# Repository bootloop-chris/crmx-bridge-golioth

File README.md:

# CRMX Bridge

An early demo of the [BootLoop Agent](https://bootloop.ai)!

*This repo is forked from a personal project of mine [https://github.com/chris-markus/crmx-bridge](https://github.com/chris-markus/crmx-bridge). Some clean-up commits added and upgraded to work with the most recent version of the IDF.*

Commit [77b8aad](https://github.com/bootloop-chris/crmx-bridge-golioth/commit/77b8aad5b4f520016bc5265554ae8e2e5ca4bd7b) was entirely generated and tested end-to-end by the BootLoop Agent. Email `chris [AT] bootloop [DOT] ai` for a video of the process.

---

Original README below:

Firmware and hardware for a CRMX bridge based around an ESP32s3 and a [TimoTwo module](https://lumenradio.com/products/timotwo/).

## Caveats

This is a personal project under active development. There are known (and probably unknown) bugs in the hardware. It has been open-sourced for visibility but use the hardware and firmware at your own risk!

### Known Issues

* The power button circuit has no memory outside of the microcontroller, so while downloading firmware, one of two things must be done:
  * Jump J105 to disable the power button circuit and unconditionally power the device while USB is connected
  * Hold down the power button for the duration of the software update

## Contents

* [crmx-bridge](./crmx-bridge/) - Hardware design files for the main PCBA
* [crmx-bridge-hmi](./crmx-bridge-hmi/) - Hardware design files for the Interface PCBA
* [crmx-bridge-firmware](./crmx-bridge-firmware/) - Firmware for the ESP32s3

## Firmware

Note that the firmware is pretty incomplete. It has a subset of functionality (can forward wired DMX to CRMX) but lacks control over most settings via the HMI among other omissions.

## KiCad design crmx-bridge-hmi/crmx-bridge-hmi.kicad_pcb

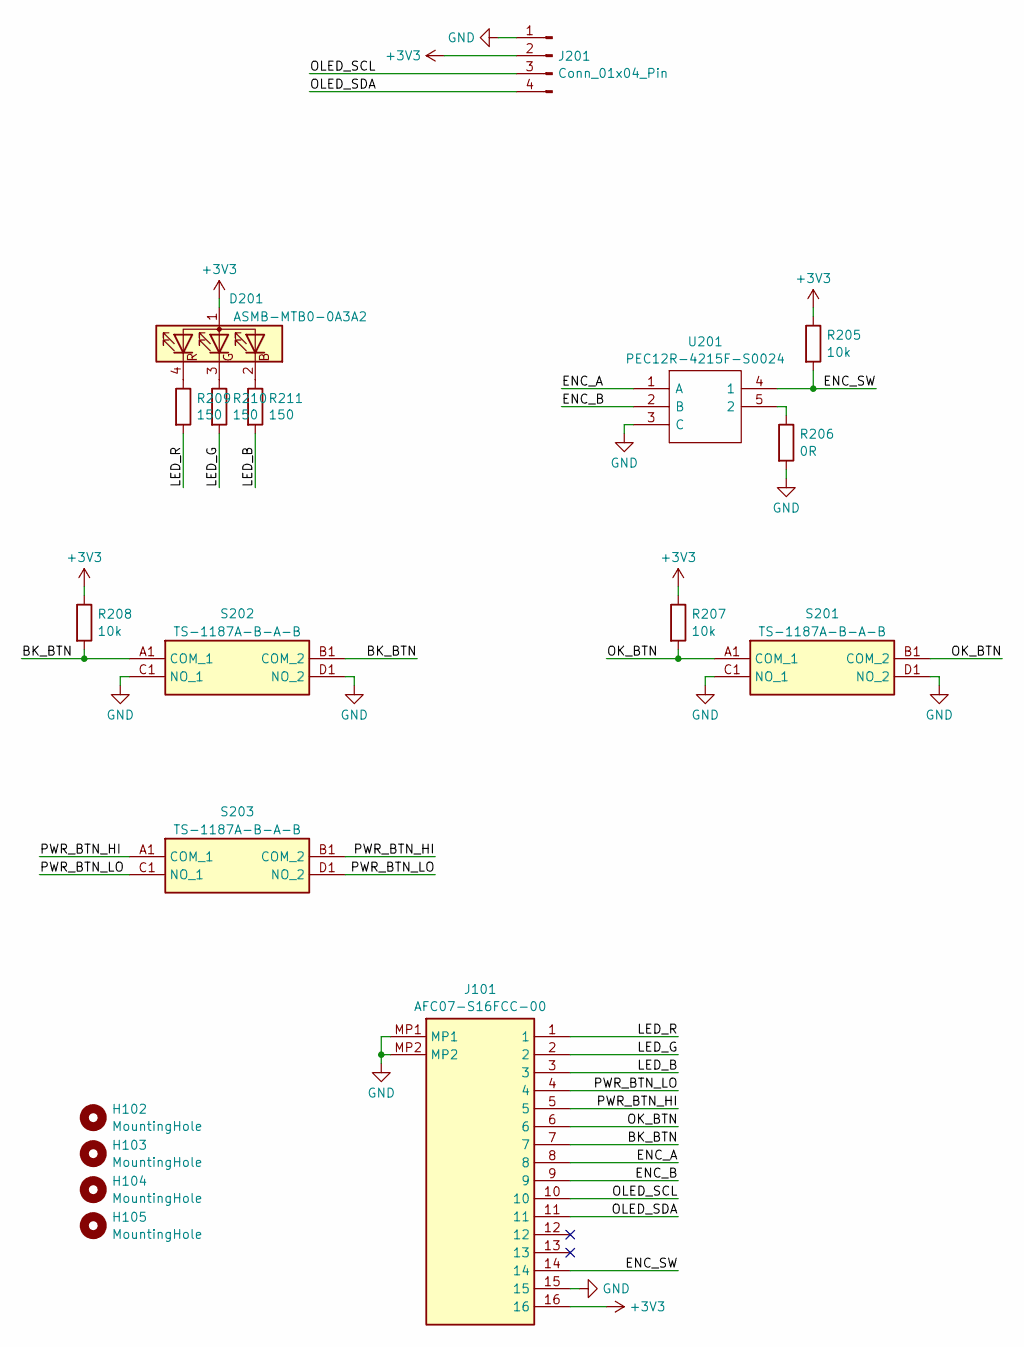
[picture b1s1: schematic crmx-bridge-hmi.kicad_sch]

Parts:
D201: ASMB-MTB0-0A3A2; ASMBMTB00A3A2
H102, H103, H104, H105: MountingHole; MountingHole_3.2mm_M3
J101: AFC07-S16FCC-00; AFC07S16FCC00; Manufacturer_Part_Number AFC07-S16FCC-00; LCSC C11053
J201: Conn_01x04_Pin; OLED_1.3
R205, R207, R208: 10k; R_0402_1005Metric; LCSC C25744
R206: 0R; R_0402_1005Metric; LCSC C17168
R209, R210, R211: 150; R_0603_1608Metric; LCSC C22808
S201, S202, S203: TS-1187A-B-A-B; TS1187ABAB; Manufacturer_Part_Number TS-1187A-B-A-B; LCSC C318884
U201: PEC12R-4215F-S0024; PEC12R-4XXXF-SXXXX; Manufacturer_Part_Number PEC12R-4215F-S0024; Mouser Part Number 652-PEC12R-4215F-S24

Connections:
+3V3: D201.1 (A), J101.16, J201.2, R205.1, R207.1, R208.1
/BK_BTN: J101.7, R208.2, S202.A1 (COM_1), S202.B1 (COM_2)
/ENC_A: J101.8, U201.1 (A)
/ENC_B: J101.9, U201.2 (B)
/ENC_SW: J101.14, R205.2, U201.4 (1)
/LED_B: J101.3, R211.2
/LED_G: J101.2, R210.2
/LED_R: J101.1, R209.2
/OK_BTN: J101.6, R207.2, S201.A1 (COM_1), S201.B1 (COM_2)
/OLED_SCL: J101.10, J201.3
/OLED_SDA: J101.11, J201.4
/PWR_BTN_HI: J101.5, S203.A1 (COM_1), S203.B1 (COM_2)
/PWR_BTN_LO: J101.4, S203.C1 (NO_1), S203.D1 (NO_2)
GND: J101.15, J101.MP1, J101.MP2, J201.1, R206.2, S201.C1 (NO_1), S201.D1 (NO_2), S202.C1 (NO_1), S202.D1 (NO_2), U201.3 (C)
unnamed: D201.2 (BK), R211.1
unnamed: D201.3 (GK), R210.1
unnamed: D201.4 (RK), R209.1
unnamed: R206.1, U201.5 (2)

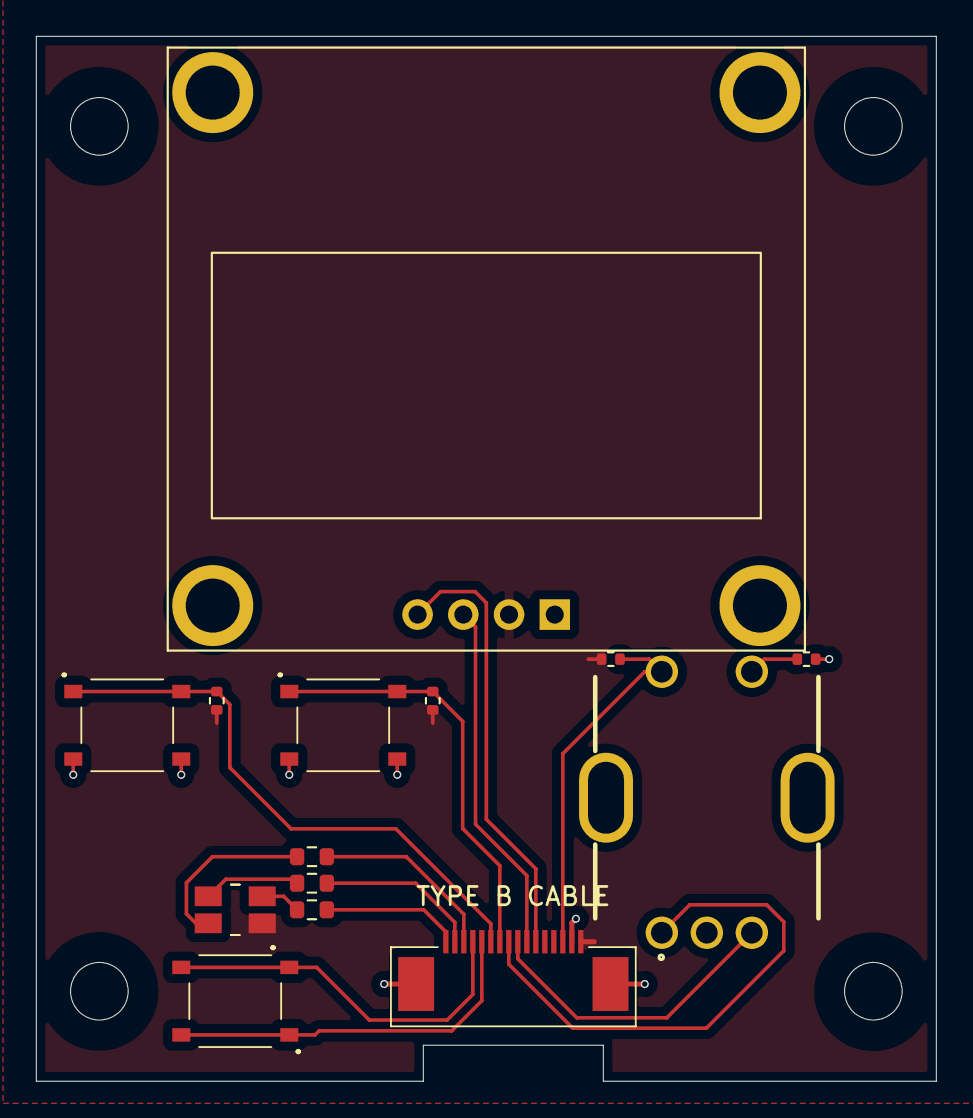
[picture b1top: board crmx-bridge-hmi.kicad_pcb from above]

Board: 2 copper layers, 50.0 x 58.0 mm, 18 parts (0 on the bottom side), 18 nets.

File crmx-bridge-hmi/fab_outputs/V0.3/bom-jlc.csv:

Designator,Footprint,Quantity,Value,LCSC Part #
J101,AFC07S16FCC00,1,AFC07-S16FCC-00,C11053
"R205, R207, R208",0402,3,10k,C25744
R206,0402,1,0R,C17168
"R209, R210, R211",0603,3,150,C22808
"S201, S202, S203",TS1187ABAB,3,TS-1187A-B-A-B,C318884

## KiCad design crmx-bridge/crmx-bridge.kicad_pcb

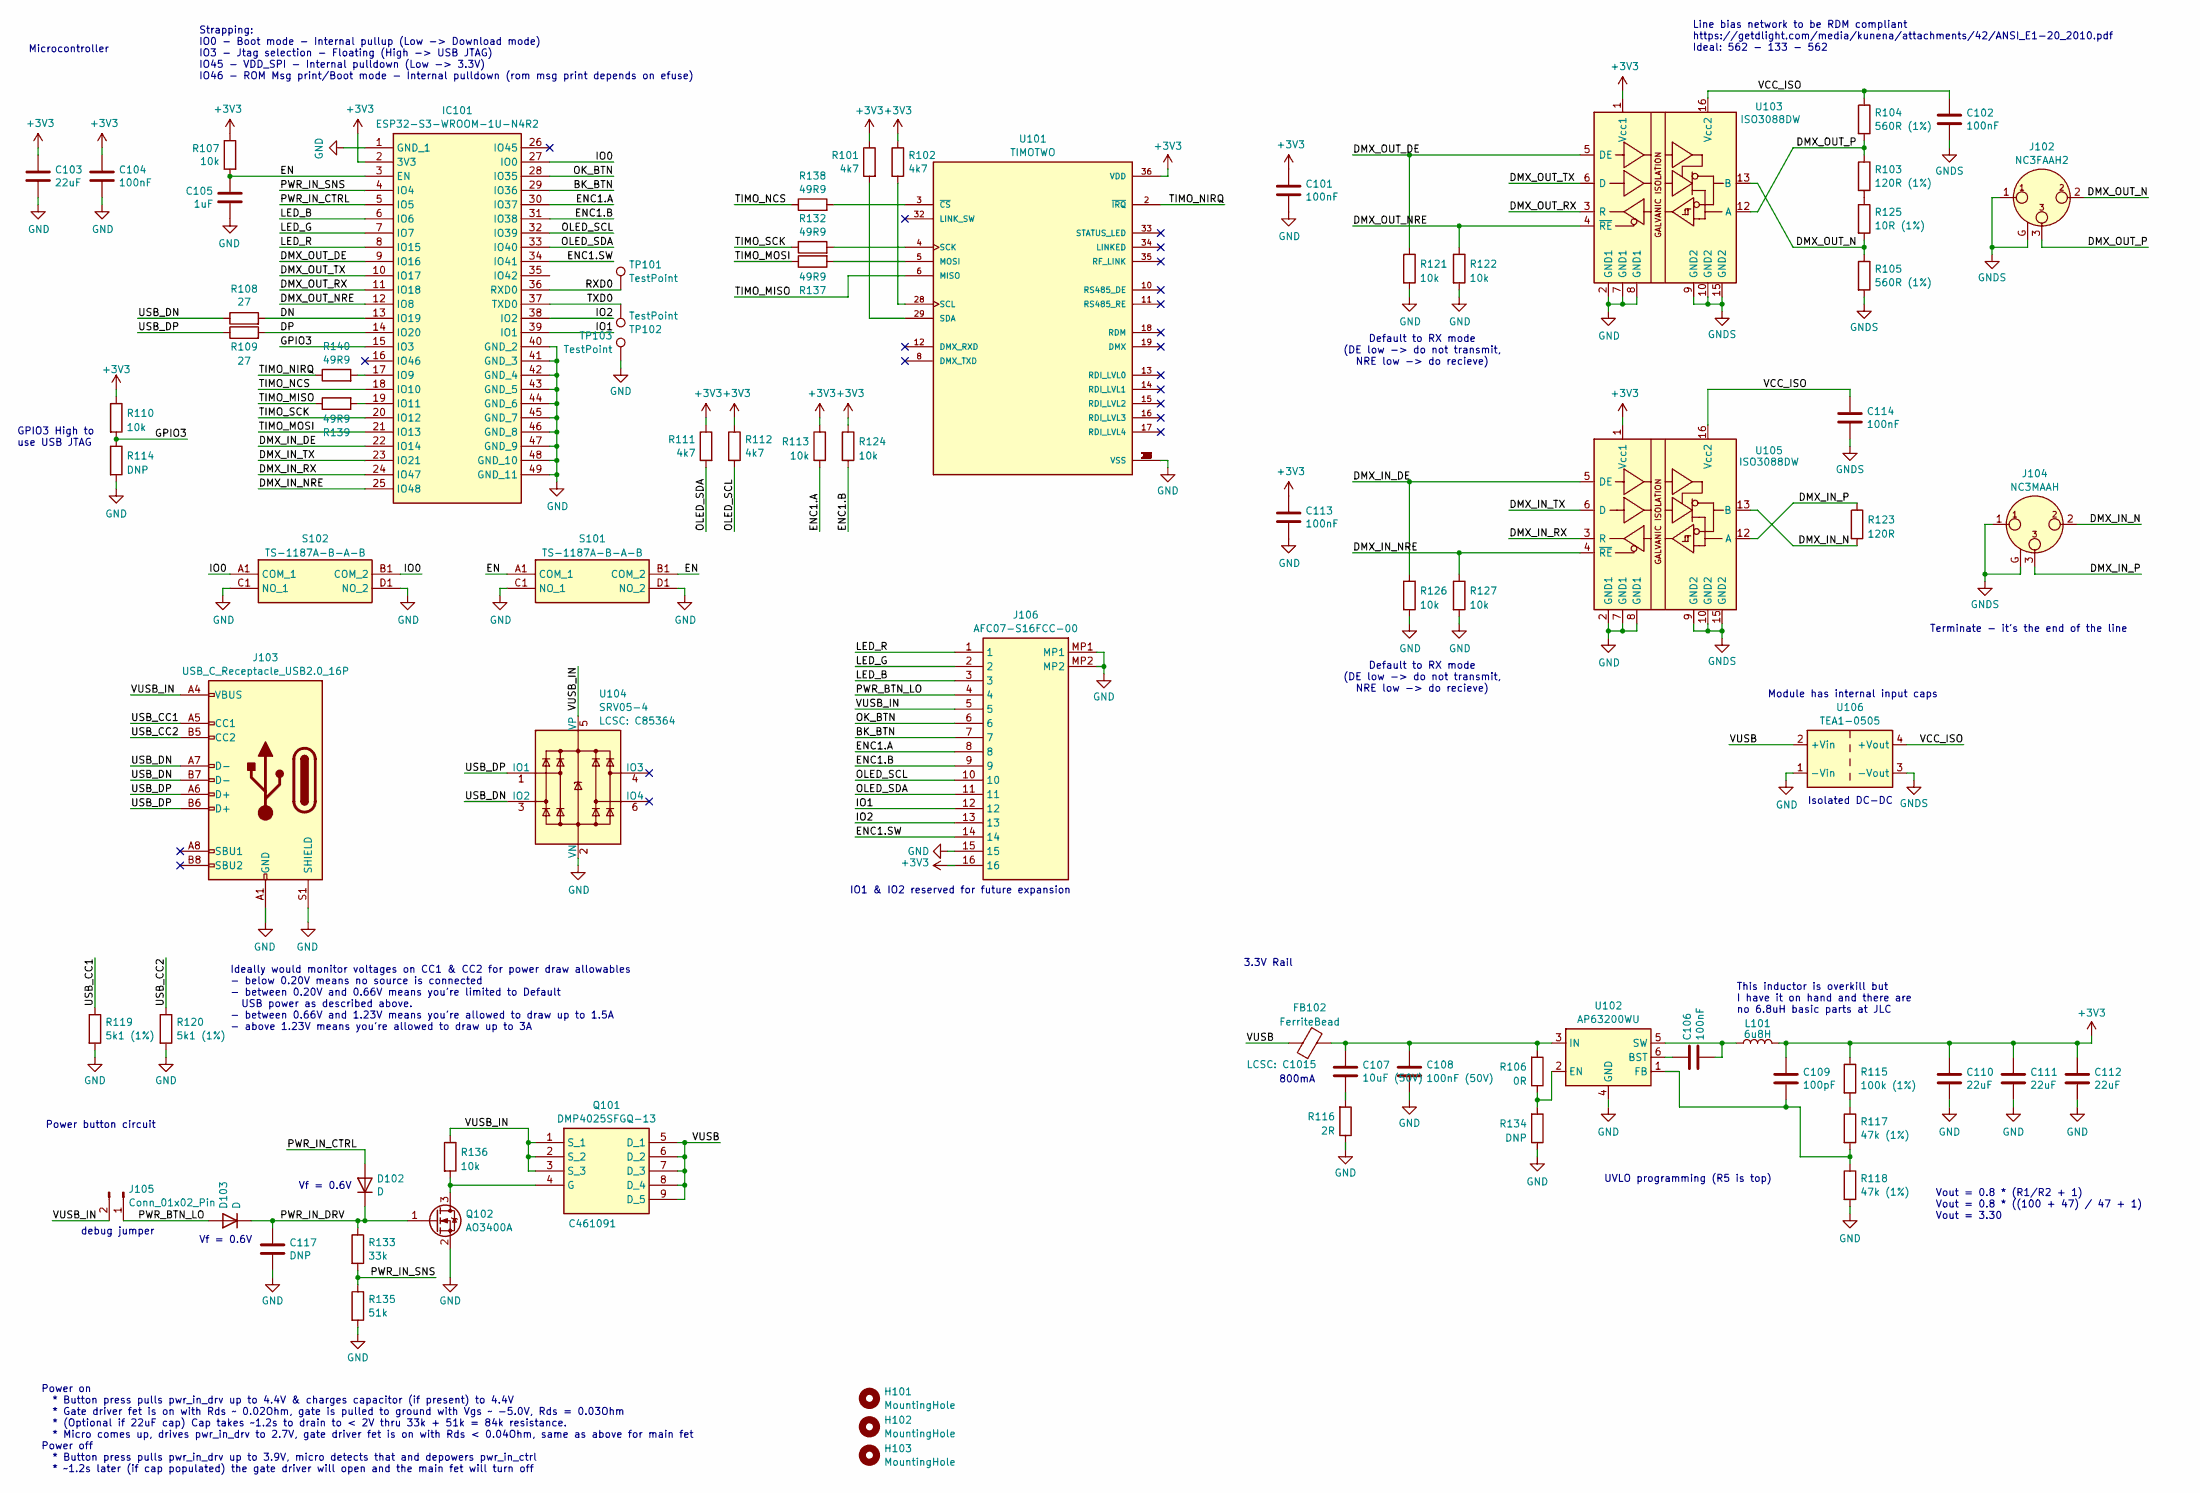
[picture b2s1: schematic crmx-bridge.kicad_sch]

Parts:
C101, C102, C104, C106, C113, C114: 100nF; C_0402_1005Metric; LCSC C1525
C103, C110, C111, C112: 22uF; C_1206_3216Metric; LCSC C12891
C105: 1uF; C_0603_1608Metric; LCSC C15849
C107: 10uF (50V); C_0603_1608Metric; LCSC C96446
C108: 100nF (50V); C_0402_1005Metric; LCSC C1525
C109: 100pF; C_0603_1608Metric; LCSC C14858
C117: DNP; C_1206_3216Metric; LCSC C12891
D102, D103: D; D_SOD-323; LCSC C191023
FB102: FerriteBead; C_0805_2012Metric; LCSC C1015
H101, H102, H103: MountingHole; MountingHole_3.2mm_M3
IC101: ESP32-S3-WROOM-1U-N4R2; ESP32S3WROOM1UN4R2; Manufacturer_Part_Number ESP32-S3-WROOM-1U-N4R2; Mouser Part Number 356-ESP32S3WRM1UN4R2
J102: NC3FAAH2; Jack_XLR_Neutrik_NC3FAAH2_Horizontal
J103: USB_C_Receptacle_USB2.0_16P; USB_C_Receptacle_HRO_TYPE-C-31-M-12; LCSC C165948
J104: NC3MAAH; Jack_XLR_Neutrik_NC3MAAH_Horizontal
J105: Conn_01x02_Pin; PinHeader_1x02_P2.54mm_Vertical
J106: AFC07-S16FCC-00; AFC07S16FCC00; Manufacturer_Part_Number AFC07-S16FCC-00; LCSC C11053
L101: 6u8H; L_Bourns_SRP7028A_7.3x6.6mm
Q101: DMP4025SFGQ-13; DMTH8008LFGQ7; Manufacturer_Part_Number DMPH4029LFGQ-13; Mouser Part Number 621-DMPH4029LFGQ-13
Q102: AO3400A; SOT-23; LCSC C20917
R101, R102, R111, R112: 4k7; R_0402_1005Metric; LCSC C25900
R103: 120R (1%); R_0603_1608Metric; LCSC C22787
R104, R105: 560R (1%); R_0603_1608Metric; LCSC C23204
R106: 0R; R_0402_1005Metric; LCSC C17168
R107, R110, R113, R121, R122, R124, R126, R127, R136: 10k; R_0402_1005Metric; LCSC C25744
R108, R109: 27; R_0603_1608Metric; LCSC C25190
R114, R134: DNP; R_0402_1005Metric
R115: 100k (1%); R_0402_1005Metric; LCSC C25741
R116: 2R; R_0603_1608Metric; LCSC C22977
R117, R118: 47k (1%); R_0402_1005Metric; LCSC C25792
R119, R120: 5k1 (1%); R_0402_1005Metric; LCSC C25905
R123: 120R; R_0603_1608Metric; LCSC C22787
R125: 10R (1%); R_0603_1608Metric; LCSC C22859
R132, R137, R138, R139, R140: 49R9; R_0402_1005Metric; LCSC C25120
R133: 33k; R_0402_1005Metric; LCSC C25779
R135: 51k; R_0402_1005Metric; LCSC C25794
S101, S102: TS-1187A-B-A-B; TS1187ABAB; Manufacturer_Part_Number TS-1187A-B-A-B; LCSC C318884
TP101, TP102, TP103: TestPoint; TestPoint_Pad_D1.5mm
U101: TIMOTWO; MODULE_TIMOTWO; PARTREV N/A
U102: AP63200WU; TSOT-23-6; LCSC C2071868
U103, U105: ISO3088DW; SOIC-16W_7.5x10.3mm_P1.27mm; LCSC C39386
U104: SRV05-4; SOT-23-6; LCSC C85364
U106: TEA1-0505; Converter_DCDC_TRACO_TEA1-xxxx_THT

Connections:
+3V3: C101.1, C103.1, C104.1, C109.1, C110.1, C111.1, C112.1, C113.1, IC101.2 (3V3), J106.16, L101.2, R101.1, R102.1, R107.1, R110.1, R111.1, R112.1, R113.1, R115.1, R124.1, U101.36 (VDD), U103.1 (Vcc1), U105.1 (Vcc1)
/BK_BTN: IC101.29 (IO36), J106.7
/DMX_IN_DE: IC101.22 (IO14), R126.1, U105.5 (DE)
/DMX_IN_N: J104.2, R123.2, U105.13 (B)
/DMX_IN_NRE: IC101.25 (IO48), R127.1, U105.4 (~RE)
/DMX_IN_P: J104.3, R123.1, U105.12 (A)
/DMX_IN_RX: IC101.24 (IO47), U105.3 (R)
/DMX_IN_TX: IC101.23 (IO21), U105.6 (D)
/DMX_OUT_DE: IC101.9 (IO16), R121.1, U103.5 (DE)
/DMX_OUT_N: J102.2, R105.1, R125.2, U103.13 (B)
/DMX_OUT_NRE: IC101.12 (IO8), R122.1, U103.4 (~RE)
/DMX_OUT_P: J102.3, R103.1, R104.2, U103.12 (A)
/DMX_OUT_RX: IC101.11 (IO18), U103.3 (R)
/DMX_OUT_TX: IC101.10 (IO17), U103.6 (D)
/DN: IC101.13 (IO19), R108.2
/DP: IC101.14 (IO20), R109.2
/EN: C105.1, IC101.3 (EN), R107.2, S101.A1 (COM_1), S101.B1 (COM_2)
/ENC1.A: IC101.30 (IO37), J106.8, R113.2
/ENC1.B: IC101.31 (IO38), J106.9, R124.2
/ENC1.SW: IC101.34 (IO41), J106.14
/GPIO3: IC101.15 (IO3), R110.2, R114.1
/IO0: IC101.27 (IO0), S102.A1 (COM_1), S102.B1 (COM_2)
/IO1: IC101.39 (IO1), J106.12
/IO2: IC101.38 (IO2), J106.13
/LED_B: IC101.6 (IO6), J106.3
/LED_G: IC101.7 (IO7), J106.2
/LED_R: IC101.8 (IO15), J106.1
/OK_BTN: IC101.28 (IO35), J106.6
/OLED_SCL: IC101.32 (IO39), J106.10, R112.2
/OLED_SDA: IC101.33 (IO40), J106.11, R111.2
/PWR_BTN_LO: D103.2 (A), J105.1, J106.4
/PWR_IN_CTRL: D102.2 (A), IC101.5 (IO5)
/PWR_IN_DRV: C117.1, D102.1 (K), D103.1 (K), Q102.1 (G), R133.1
/PWR_IN_SNS: IC101.4 (IO4), R133.2, R135.1
/RXD0: IC101.36 (RXD0), TP101.1
/TIMO_MISO: R139.1, U101.6 (MISO)
/TIMO_MOSI: IC101.21 (IO13), R137.1
/TIMO_NCS: IC101.18 (IO10), R138.1
/TIMO_NIRQ: R140.1, U101.2 (~IRQ)
/TIMO_SCK: IC101.20 (IO12), R132.1
/TXD0: IC101.37 (TXD0), TP102.1
/USB_CC1: J103.A5 (CC1), R119.1
/USB_CC2: J103.B5 (CC2), R120.1
/USB_DN: J103.A7 (D-), J103.B7 (D-), R108.1, U104.3 (IO2)
/USB_DP: J103.A6 (D+), J103.B6 (D+), R109.1, U104.1 (IO1)
/VCC_ISO: C102.1, C114.1, R104.1, U103.16 (Vcc2), U105.16 (Vcc2), U106.4 (+Vout)
/VUSB: FB102.1, Q101.5 (D_1), Q101.6 (D_2), Q101.7 (D_3), Q101.8 (D_4), Q101.9 (D_5), U106.2 (+Vin)
/VUSB_IN: J103.A4 (VBUS), J103.A9 (VBUS), J103.B4 (VBUS), J103.B9 (VBUS), J105.2, J106.5, Q101.1 (S_1), Q101.2 (S_2), Q101.3 (S_3), R136.1, U104.5 (VP)
GND: C101.2, C103.2, C104.2, C105.2, C108.2, C110.2, C111.2, C112.2, C113.2, C117.2, IC101.1 (GND_1), IC101.40 (GND_2), IC101.41 (GND_3), IC101.42 (GND_4), IC101.43 (GND_5), IC101.44 (GND_6), IC101.45 (GND_7), IC101.46 (GND_8), IC101.47 (GND_9), IC101.48 (GND_10), IC101.49 (GND_11), J103.A1 (GND), J103.A12 (GND), J103.B1 (GND), J103.B12 (GND), J103.S1 (SHIELD), J106.15, J106.MP1, J106.MP2, Q102.2 (S), R114.2, R116.1, R118.2, R119.2, R120.2, R121.2, R122.2, R126.2, R127.2, R134.1, R135.2, S101.C1 (NO_1), S101.D1 (NO_2), S102.C1 (NO_1), S102.D1 (NO_2), TP103.1, U101.1 (VSS), U101.7 (VSS), U101.9 (VSS), U101.22 (VSS), U101.23 (VSS), U101.24 (VSS), U101.25 (VSS), U101.26 (VSS), U101.27 (VSS), U101.30 (VSS), U101.37 (VSS), U102.4 (GND), U103.2 (GND1), U103.7 (GND1), U103.8 (GND1), U104.2 (VN), U105.2 (GND1), U105.7 (GND1), U105.8 (GND1), U106.1 (-Vin)
GNDS: C102.2, C114.2, J102.1, J102.G, J104.1, J104.G, R105.2, U103.9 (GND2), U103.10 (GND2), U103.15 (GND2), U105.9 (GND2), U105.10 (GND2), U105.15 (GND2), U106.3 (-Vout)
unnamed: C107.2, R116.2
unnamed: IC101.17 (IO9), R140.2
unnamed: IC101.19 (IO11), R139.2
unnamed: Q101.4 (G), Q102.3 (D), R136.2
unnamed: R103.2, R125.1
unnamed: R115.2, R117.1
unnamed: R137.2, U101.5 (MOSI)
unnamed: R132.2, U101.4 (SCK)
unnamed: R102.2, U101.28 (SCL)
unnamed: R101.2, U101.29 (SDA)
unnamed: R138.2, U101.3 (~CS)
unnamed: C106.1, U102.6 (BST)
unnamed: R106.1, R134.2, U102.2 (EN)
unnamed: C109.2, R117.2, R118.1, U102.1 (FB)
unnamed: C107.1, C108.1, FB102.2, R106.2, U102.3 (IN)
unnamed: C106.2, L101.1, U102.5 (SW)

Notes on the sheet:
Power on * Button press pulls pwr_in_drv up to 4.4V & charges capacitor (if present) to 4.4V * Gate driver fet is on with Rds ~ 0.02Ohm, gate is pulled to ground with Vgs ~ -5.0V, Rds = 0.03Ohm * (Optional if 22uF cap) Cap takes ~1.2s to drain to < 2V thru 33k + 51k = 84k resistance. * Micro comes 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
Vout = 0.8 * (R1/R2 + 1) Vout = 0.8 * ((100 + 47) / 47 + 1) Vout = 3.30
Vf = 0.6V
GPIO3 High to use USB JTAG
Strapping: IO0 - Boot mode - Internal pullup (Low -> Download mode) IO3 - Jtag selection - Floating (High -> USB JTAG) IO45 - VDD_SPI - Internal pulldown (Low -> 3.3V) IO46 - ROM Msg print/Boot mode - Internal pulldown (rom msg print depends on efuse)
debug jumper
3.3V Rail
Isolated DC-DC
IO1 & IO2 reserved for future expansion
Ideally would monitor voltages on CC1 & CC2 for power draw allowables - below 0.20V means no source is connected - between 0.20V and 0.66V means you're limited to Default USB power as described above. - between 0.66V and 1.23V means you're allowed to draw up to 1.5A - above 1.23V means you're allow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
UVLO programming (R5 is top)
800mA
Default to RX mode (DE low -> do not transmit, NRE low -> do recieve)
Power button circuit
Terminate - it's the end of the line
Microcontroller
Module has internal input caps
Line bias network to be RDM compliant https://getdlight.com/media/kunena/attachments/42/ANSI_E1-20_2010.pdf Ideal: 562 - 133 - 562
This inductor is overkill but I have it on hand and there are no 6.8uH basic parts at JLC

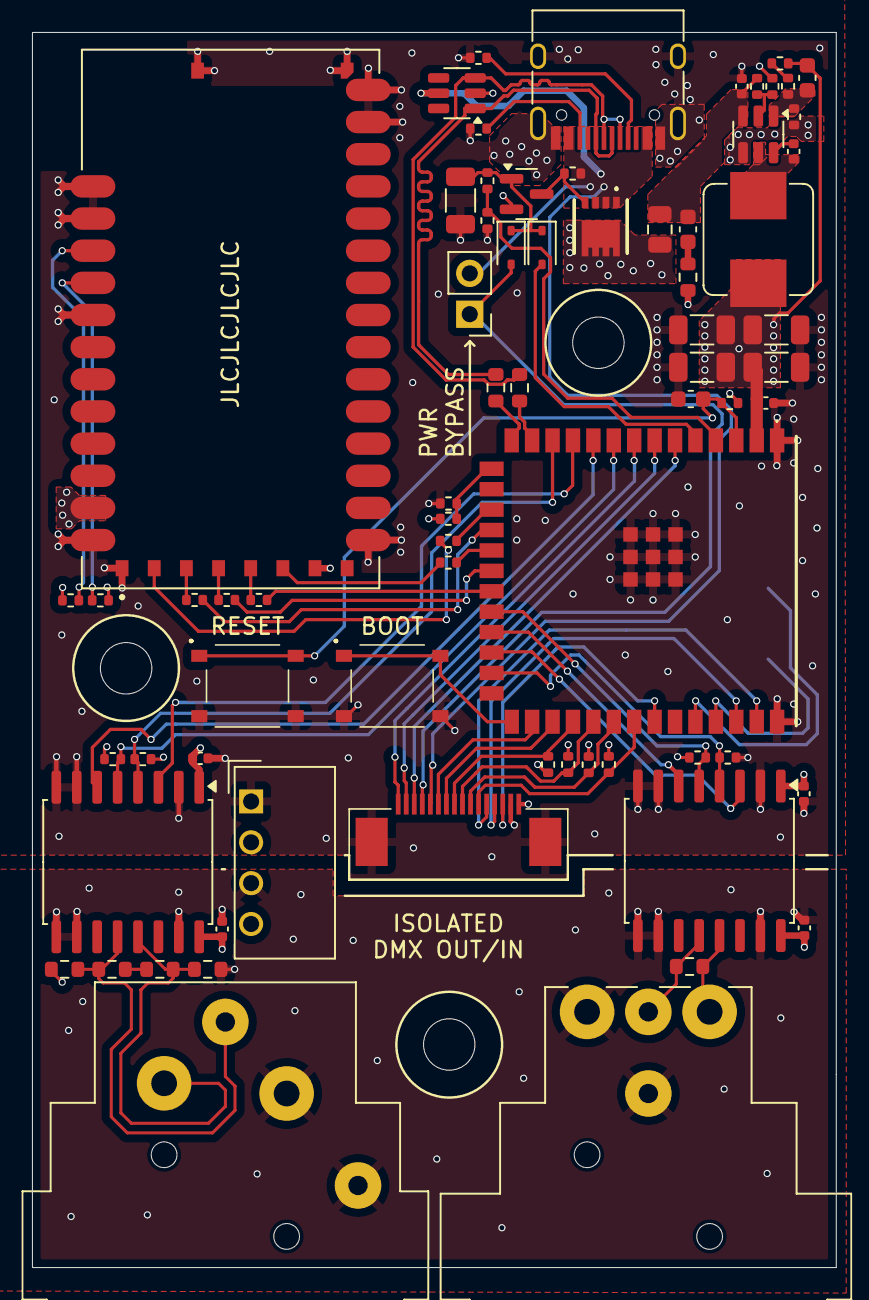
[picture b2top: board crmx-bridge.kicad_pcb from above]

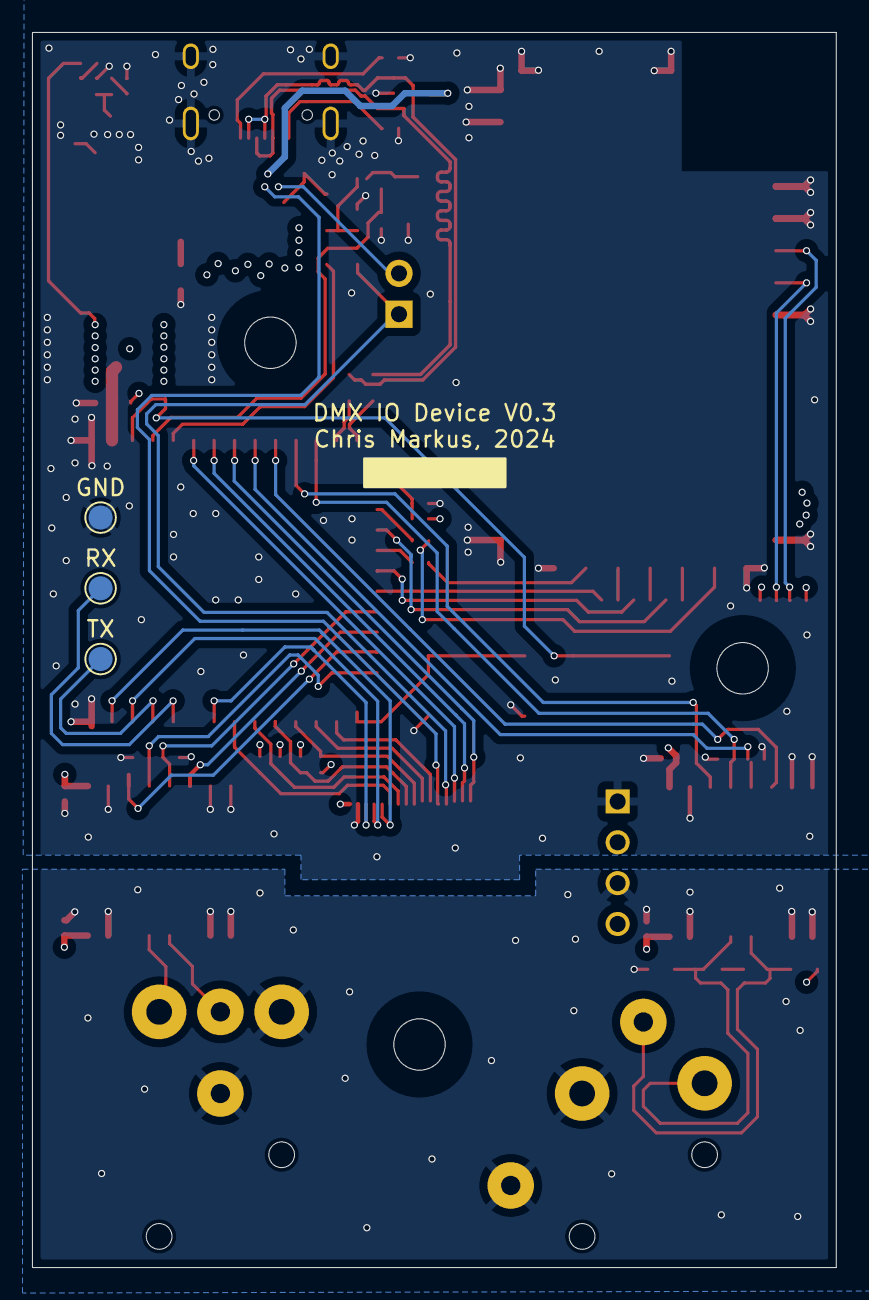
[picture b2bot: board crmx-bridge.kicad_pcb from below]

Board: 4 copper layers, 50.0 x 76.8 mm, 77 parts (3 on the bottom side), 66 nets.

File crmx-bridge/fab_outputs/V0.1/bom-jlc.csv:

Designator,Footprint,Quantity,Value,LCSC Part #
"C101, C102, C104, C106, C113, C114",0402,6,100nF,C1525
"C103, C110, C111, C112",1206,4,22uF,C12891
C105,0603,1,1uF,C15849
C107,0603,1,10uF  (50V),C96446
C108,0402,1,100nF  (50V),C1525
C109,0603,1,100pF,C14858
C117,1206,1,DNP,C12891
"D102, D103",D_SOD-323,2,D,C191023
FB102,0805,1,FerriteBead,C1015
IC101,ESP32S3WROOM1UN4R2,1,ESP32-S3-WROOM-1U-N4R2,C3013942
"J101, J106",AFC07S16FCC00,2,AFC07-S16FCC-00,C11053
J103,USB_C_Receptacle_HRO_TYPE-C-31-M-12,1,USB_C_Receptacle_USB2.0_16P,C165948
Q101,DMTH8008LFGQ7,1,DMP4025SFGQ-13,C461091
Q102,SOT-23,1,AO3400A,C20917
"R101, R102, R111, R112",0402,4,4k7,C25900
R103,0603,1,120R (1%),C22787
"R104, R105",0603,2,560R (1%),C23204
"R106, R206",0402,2,0R,C17168
"R107, R110, R113, R121, R122, R124, R126, R127, R136, R205, R207, R208",0402,12,10k,C25744
"R108, R109",0603,2,27,C25190
R115,0402,1,100k (1%),C25741
R116,0603,1,2R,C22977
"R117, R118",0402,2,47k (1%),C25792
"R119, R120",0402,2,5k1 (1%),C25905
R123,0603,1,120R,C22787
R125,0603,1,10R (1%),C22859
"R132, R137, R138, R139, R140",0402,5,49R9,C25120
R133,0402,1,33k,C25779
R135,0402,1,51k,C25794
"R209, R210, R211",0603,3,150,C22808
"S101, S102, S201, S202, S203",TS1187ABAB,5,TS-1187A-B-A-B,C318884
U102,TSOT-23-6,1,AP63200WU,C2071868
"U103, U105",SOIC-16W_7.5x10.3mm_P1.27mm,2,ISO3088DW,C39386
U104,SOT-23-6,1,SRV05-4,C85364

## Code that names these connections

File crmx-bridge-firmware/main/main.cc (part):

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const static char *TAG = "main";

static constexpr adc_channel_t pwr_btn_sns_chann = ADC_CHANNEL_3;
static constexpr gpio_num_t pwr_in_ctrl_pin = GPIO_NUM_37;
static constexpr int pwr_btn_press_thresh_mv = 2500;

static constexpr spi_host_device_t timo_spi_bus = SPI2_HOST;
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
TimoInterface timo_interface{timo_config};

static constexpr gpio_num_t led_r_pin = GPIO_NUM_15;
static constexpr gpio_num_t led_g_pin = GPIO_NUM_7;
static constexpr gpio_num_t led_b_pin = GPIO_NUM_6;
static constexpr gpio_num_t btn_ok_pin = GPIO_NUM_35;
static constexpr gpio_num_t btn_bk_pin = GPIO_NUM_36;
static constexpr gpio_num_t btn_enc_pin = GPIO_NUM_41;
static constexpr gpio_num_t enc_a_pin = GPIO_NUM_37;
static constexpr gpio_num_t enc_b_pin = GPIO_NUM_38;

// DMX Configuration for physical input and output ports
struct dmx_port_config_t {
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  ESP_ERROR_CHECK(ledc_timer_config(&ledc_timer));

  static constexpr std::array<gpio_num_t, 3> led_pins = {
      {led_r_pin, led_g_pin, led_b_pin}};
  static constexpr std::array<ledc_channel_t, 3> led_channels = {
      {LEDC_CHANNEL_0, LEDC_CHANNEL_1, LEDC_CHANNEL_2}};

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  // Encoder
  rotary_encoder_info_t encoder = {};
  ESP_ERROR_CHECK(gpio_install_isr_service(0));
  ESP_ERROR_CHECK(rotary_encoder_init(&encoder, enc_a_pin, enc_b_pin));
  ESP_ERROR_CHECK(rotary_encoder_enable_half_steps(&encoder, false));

  // Create a queue for events from the rotary encoder driver.
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
  // Power pin config
  gpio_config_t io_conf = {
      .pin_bit_mask = (1ULL << pwr_in_ctrl_pin),
      .mode = GPIO_MODE_OUTPUT,
      .pull_up_en = GPIO_PULLUP_DISABLE,
      .pull_down_en = GPIO_PULLDOWN_DISABLE,
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  ESP_ERROR_CHECK(gpio_config(&io_conf));

  // Hold up the power rail
  gpio_set_level(pwr_in_ctrl_pin, true);

  // Multiple drivers need NVS, settings infrastructure will initialize it.
  SettingsHandler &settings = SettingsHandler::shared();
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      if (esp_timer_get_time() - pwr_btn_press_start > 1000000) {
        ESP_LOGI(TAG, "Power button press detected, powering down.");
        vTaskDelay(pdMS_TO_TICKS(1000));
        gpio_set_level(pwr_in_ctrl_pin, false);
        vTaskDelay(portMAX_DELAY);
      }
    }
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
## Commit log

2024-11-11 Hardware V0.1
2024-11-11 updated to use FPC cable
2024-11-11 deleted backups
2024-11-11 updated gitignore
2024-11-11 Updated 3d models
2024-11-11 before rearranging
2024-11-12 smaller isolated supplies integrated, may re-arrange some more
2024-11-12 Rev to v0.2
2024-11-12 Finished layout with smaller power converters
2024-11-20 Split up PCBs into separate files, Ordered V0.3
2025-01-03 dev-ing on firmware
2025-01-05 Working hardwire DMX to CRMX
2025-01-06 added rotary encoder submodule
2025-01-23 Halfway through UI infra implementation
2025-01-23 patched encoder submodule
2025-01-25 Initial UI functional, not hooked to back-end
2025-01-25 few more UI fixes
2025-07-19 Get settings working on display
2025-07-19 remove rotary encoder submodule
2025-07-19 add rotary encoder component as manual fork
2025-07-19 Remove esp_dmx submodule
2025-07-19 Add esp_dmx manual fork
2025-07-19 remove sdkconfig from gitignore
2025-07-19 Update IDF version
2025-07-19 Add SDKConfig
2025-07-19 Restore sdkconfig from crmx-bridge
2025-07-19 Auto-update sdkconfig for new idf version
2025-07-19 hardcoded settings, fixed timo driver delays
2025-07-19 Add golioth submodule
2025-07-20 Add wifi to the app and make some cleanups
2025-07-20 Golioth demo - Agent generated (redacted credentials)
2025-07-23 Add README
